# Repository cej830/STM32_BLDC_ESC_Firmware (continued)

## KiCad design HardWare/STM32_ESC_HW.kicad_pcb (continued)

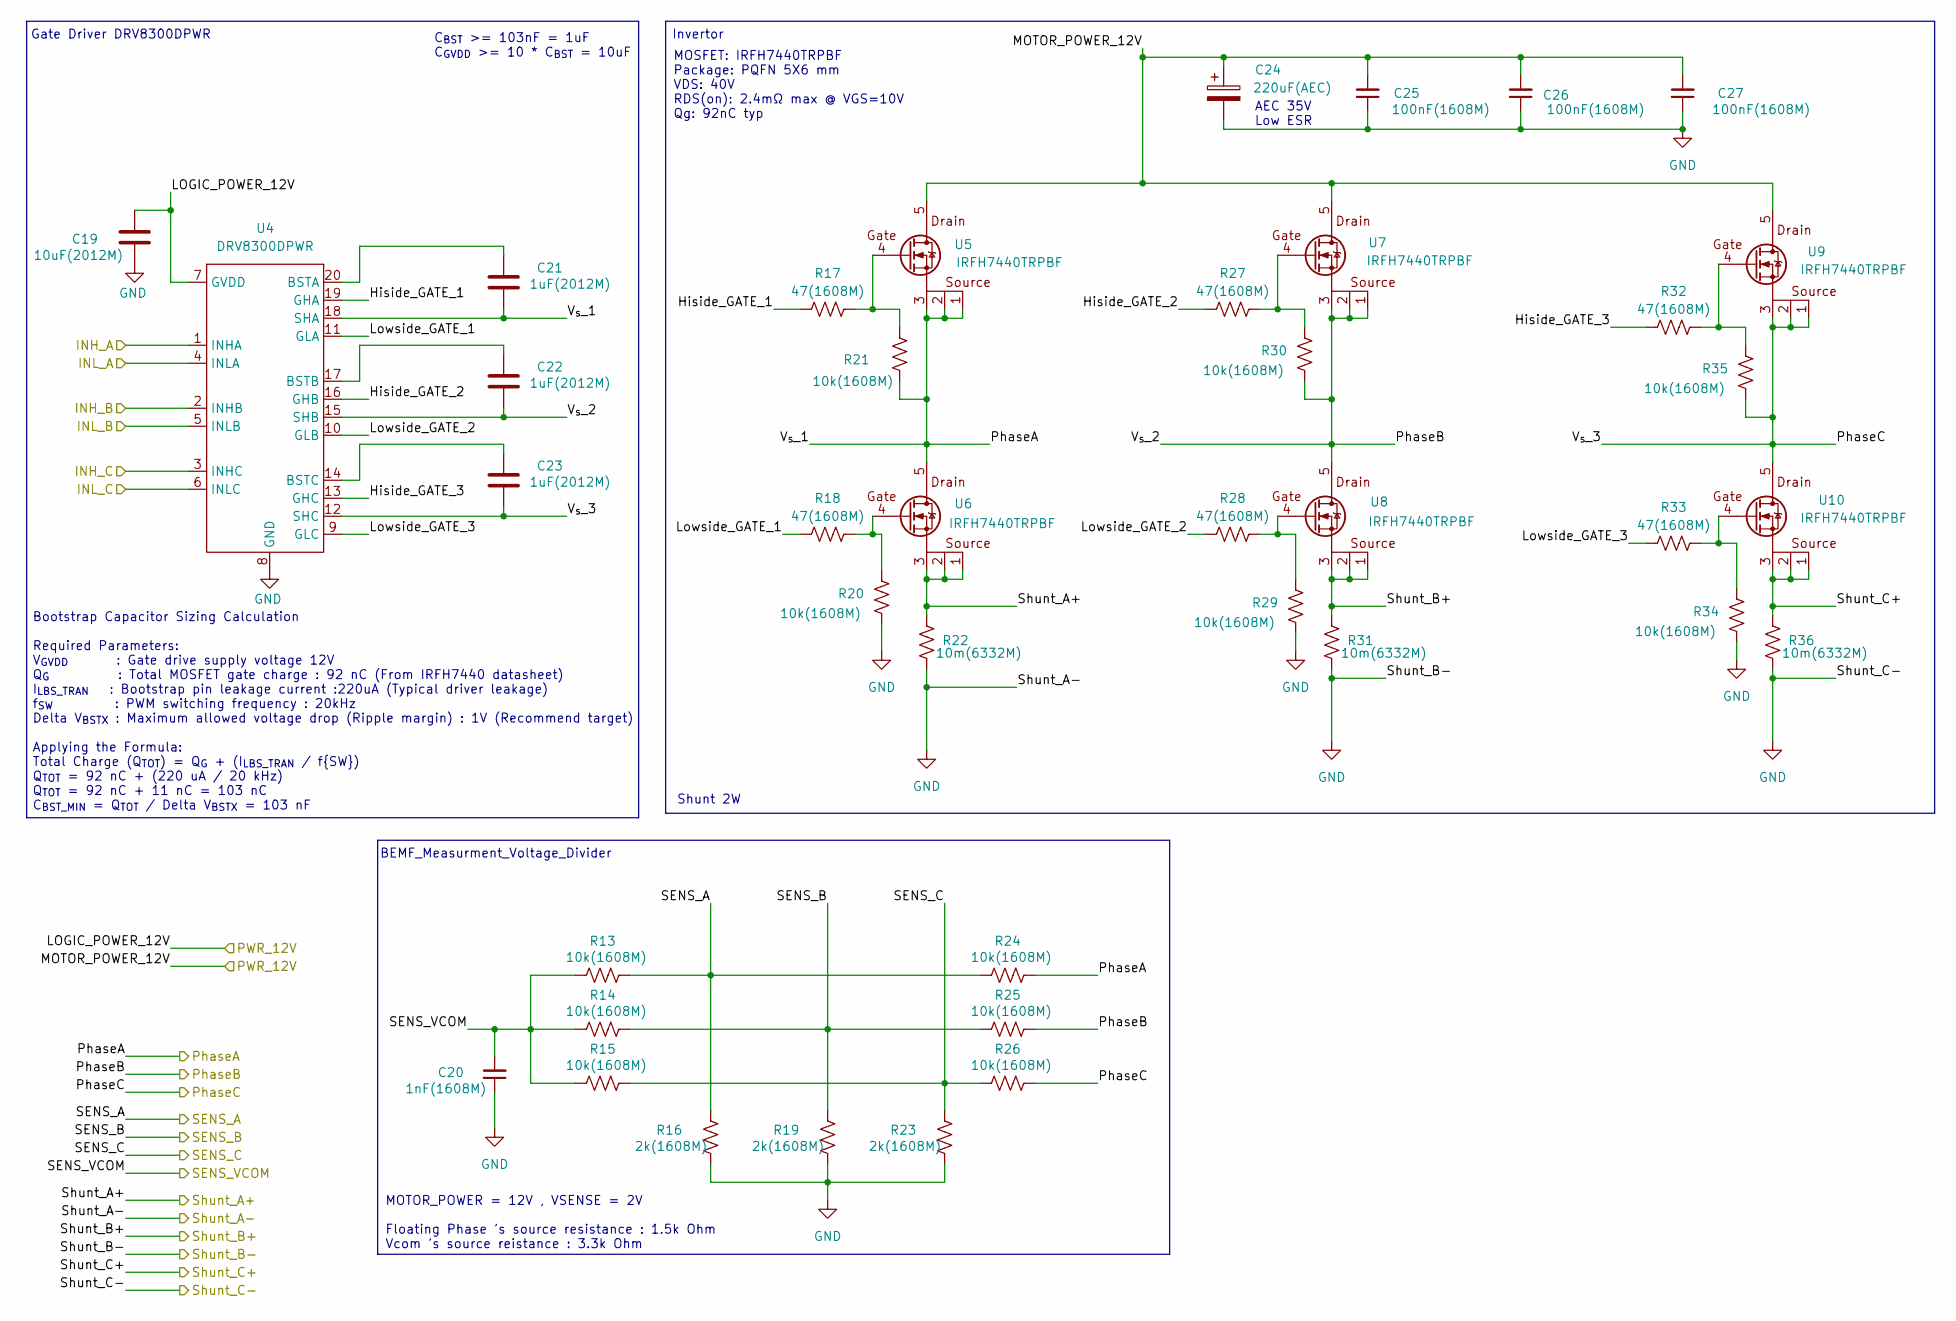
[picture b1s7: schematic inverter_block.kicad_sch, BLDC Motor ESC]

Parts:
C19: 10uF(2012M); C_0805_2012Metric; Part number CL21A106KAYNNNE
C20: 1nF(1608M); C_0603_1608Metric; Part number CL10B102KB8NNNC
C21, C22, C23: 1uF(2012M); C_0805_2012Metric; Part number CL21B105KAFNFNE
C24: 220uF(AEC); CP_Elec_8x10.5; Part number RVT1V221M0810
C25, C26, C27: 100nF(1608M); C_0603_1608Metric; Part number GRM188R71H104KA93D
R13, R14, R15, R20, R21, R24, R25, R26, R29, R30, R34, R35: 10k(1608M); R_0603_1608Metric; Part number 0603WAF1002T5E
R16, R19, R23: 2k(1608M); R_0603_1608Metric; Part number 0603WAF2001T5E
R17, R18, R27, R28, R32, R33: 47(1608M); R_0603_1608Metric; Part number 0603WAF470JT5E
R22, R31, R36: 10m(6332M); Shunt_R_PE2512_7m-910m Ohm_SMD_2512; Part number PE2512FKE7W0R01Z
U4: DRV8300DPWR; DRV8300DPWR 20-TSSOP 6.6mm _ 4.5mm; Part number DRV8300DPWR
U5, U6, U7, U8, U9, U10: IRFH7440TRPBF; PQFN-8-EP_6x5mm_P1.27mm_Generic; Part number IRFH7440TRPBF

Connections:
+12V: C19.1, C24.1, C25.2, C26.2, C27.2, U4.7 (GVDD), U5.5, U7.5, U9.5; also elsewhere on the board
/Inverter_BLOCK/Hiside_GATE_1: R17.1, U4.19 (GHA)
/Inverter_BLOCK/Hiside_GATE_2: R27.1, U4.16 (GHB)
/Inverter_BLOCK/Hiside_GATE_3: R32.1, U4.13 (GHC)
/Inverter_BLOCK/Lowside_GATE_1: R18.1, U4.11 (GLA)
/Inverter_BLOCK/Lowside_GATE_2: R28.1, U4.10 (GLB)
/Inverter_BLOCK/Lowside_GATE_3: R33.1, U4.9 (GLC)
/Inverter_BLOCK/PhaseA: C21.1, R21.2, R24.2, U4.18 (SHA), U5.1, U5.2, U5.3, U6.5; also elsewhere on the board
/Inverter_BLOCK/PhaseB: C22.1, R25.2, R30.2, U4.15 (SHB), U7.1, U7.2, U7.3, U8.5; also elsewhere on the board
/Inverter_BLOCK/PhaseC: C23.1, R26.2, R35.2, U4.12 (SHC), U9.1, U9.2, U9.3, U10.5; also elsewhere on the board
/Inverter_BLOCK/SENS_A: R13.2, R16.2, R24.1; also elsewhere on the board
/Inverter_BLOCK/SENS_B: R14.2, R19.2, R25.1; also elsewhere on the board
/Inverter_BLOCK/SENS_C: R15.2, R23.2, R26.1; also elsewhere on the board
/Inverter_BLOCK/SENS_VCOM: C20.2, R13.1, R14.1, R15.1; also elsewhere on the board
/Inverter_BLOCK/Shunt_A+: R22.1, U6.1, U6.2, U6.3; also elsewhere on the board
/Inverter_BLOCK/Shunt_B+: R31.1, U8.1, U8.2, U8.3; also elsewhere on the board
/Inverter_BLOCK/Shunt_C+: R36.1, U10.1, U10.2, U10.3; also elsewhere on the board
/MCU_BLOCK/PWM_CH1: U4.1 (INHA); also elsewhere on the board
/MCU_BLOCK/PWM_CH1N: U4.4 (INLA); also elsewhere on the board
/MCU_BLOCK/PWM_CH2: U4.2 (INHB); also elsewhere on the board
/MCU_BLOCK/PWM_CH2N: U4.5 (INLB); also elsewhere on the board
/MCU_BLOCK/PWM_CH3: U4.3 (INHC); also elsewhere on the board
/MCU_BLOCK/PWM_CH3N: U4.6 (INLC); also elsewhere on the board
GND: C19.2, C20.1, C24.2, C25.1, C26.1, C27.1, R16.1, R19.1, R20.2, R22.2, R23.1, R29.2, R31.2, R34.2, R36.2, U4.8 (GND); also elsewhere on the board
unnamed: R17.2, R21.1, U5.4
unnamed: R18.2, R20.1, U6.4
unnamed: R27.2, R30.1, U7.4
unnamed: R28.2, R29.1, U8.4
unnamed: R32.2, R35.1, U9.4
unnamed: R33.2, R34.1, U10.4
unnamed: C21.2, U4.20 (BSTA)
unnamed: C22.2, U4.17 (BSTB)
unnamed: C23.2, U4.14 (BSTC)

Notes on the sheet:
BEMF_Measurment_Voltage_Divider
Floating Phase 's source resistance : 1.5k Ohm Vcom 's source reistance : 3.3k Ohm
MOTOR_POWER = 12V , VSENSE = 2V
AEC 35V Low ESR
MOSFET: IRFH7440TRPBF Package: PQFN 5X6 mm VDS: 40V RDS(on): 2.4mΩ max @ VGS=10V Qg: 92nC typ
Shunt 2W
Invertor
C_{BST} >= 103nF = 1uF C_{GVDD} >= 10 * C_{BST} = 10uF
Bootstrap Capacitor Sizing Calculation Required Parameters: V_{GVDD} : Gate drive supply voltage 12V Q_{G} : Total MOSFET gate charge : 92 nC (From IRFH7440 datasheet) I_{LBS_TRAN} : Bootstrap pin leakage current :220uA (Typical driver leakage) f_{SW} : PWM switching frequency : 20kHz Delta V_{BSTX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
Gate Driver DRV8300DPWR

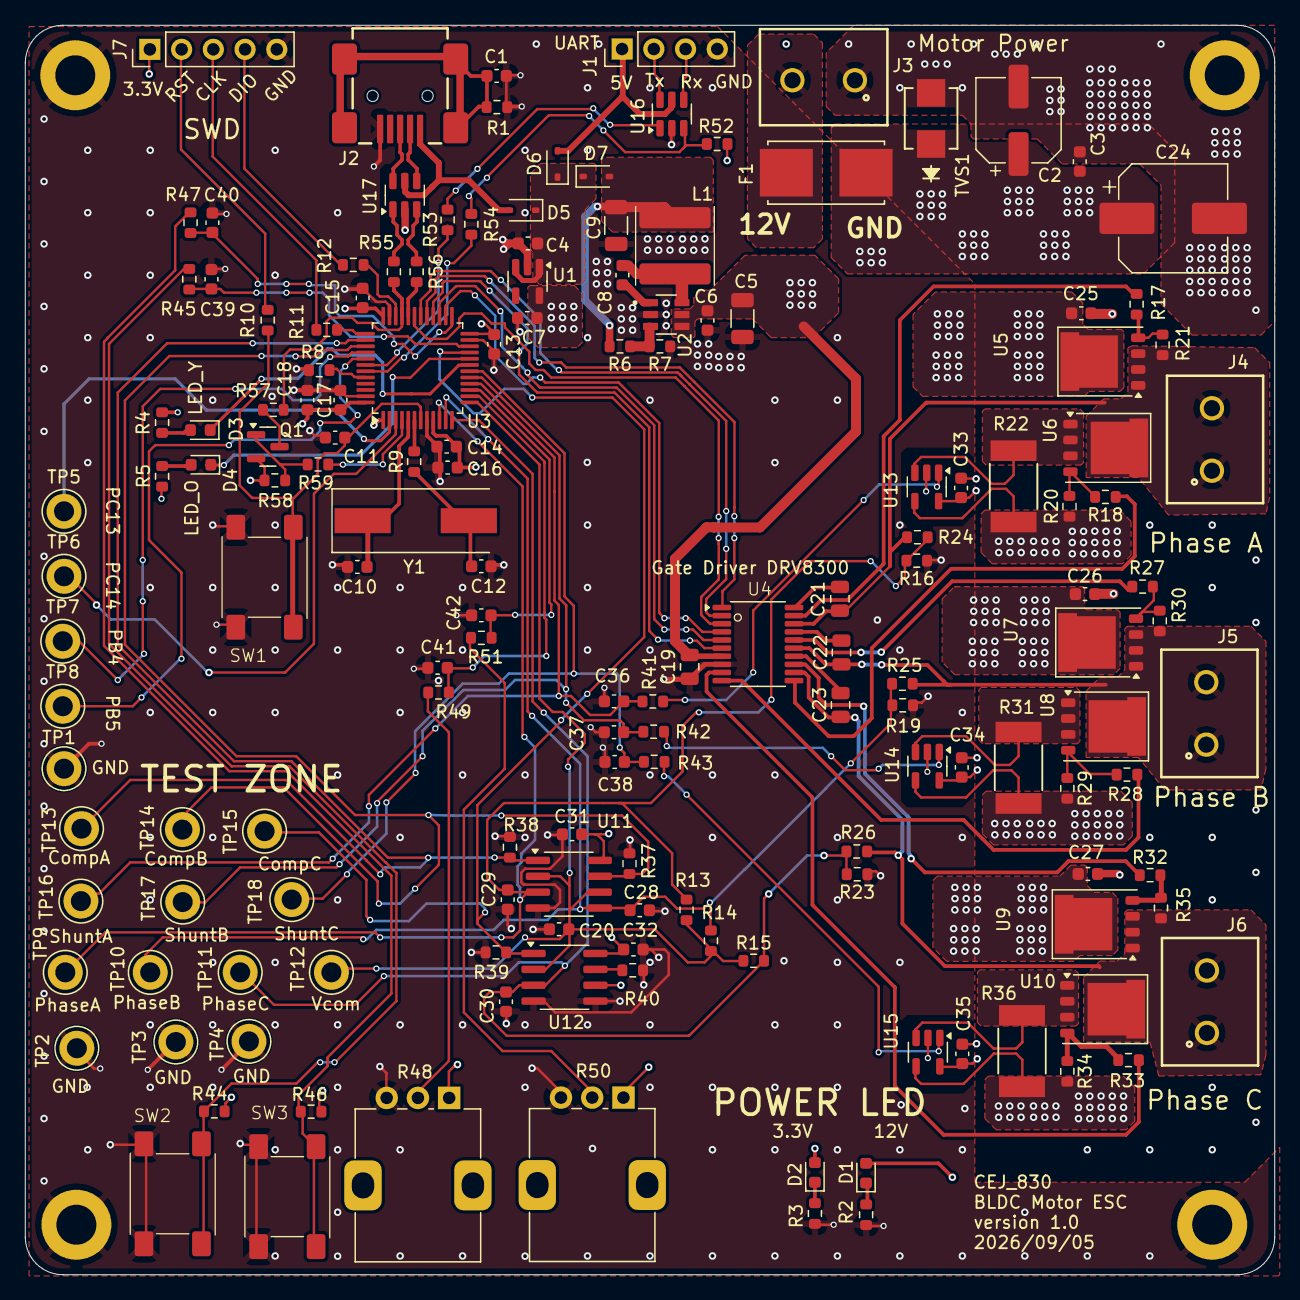
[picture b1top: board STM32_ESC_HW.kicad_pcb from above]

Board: 4 copper layers, 100.0 x 100.0 mm, 162 parts (0 on the bottom side), 96 nets.

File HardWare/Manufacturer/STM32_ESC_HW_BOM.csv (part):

"#","PKG","Reference","Value","설명","Part number","Manufacturer","Qty","Footprint","DNP","Exclude from BOM","Exclude from Board"
"1","SMD_D6.3xL7.7mm","C2","100uF(AEC)","Aluminum Electrolytic, 100uF, 35V, Low ESR","RVT1V101M0607","Honor Elec","1","Capacitor_SMD:CP_Elec_6.3x7.7","","",""
"2","SMD_1206","C5","2.2uF(3216M)","MLCC, 2.2uF, 50V, X7R, ±10%","GRM31CR71H225KA88L","Murata Electronics","1","Capacitor_SMD:C_1206_3216Metric","","",""
"3","SMD_1206","C9","22uF(3216M)","MLCC, 22uF, 10V, X7R, ±10%","GRM31CR71A226KE15L","Murata Electronics","1","Capacitor_SMD:C_1206_3216Metric","","",""
"4","SMD_0603","C14","10nF(1608M)","MLCC, 10nF, 50V, X7R, ±10%","CL10B103KB8NNNC","Samsung Electro-Mechanics","1","Capacitor_SMD:C_0603_1608Metric","","",""
"5","SMD_0805","C19","10uF(2012M)","MLCC, 10uF, 25V, X5R, ±10%","CL21A106KAYNNNE","Samsung Electro-Mechanics","1","Capacitor_SMD:C_0805_2012Metric","","",""
"6","SMD_D8_L10.2mm","C24","220uF(AEC)","Aluminum Electrolytic, 220uF, 35V, Low ESR","RVT1V221M0810","Honor Elec","1","Capacitor_SMD:CP_Elec_8x10.5","","",""
"7","SMD_0603","C1,C3,C6,C8,C11,C13,C15,C17,C25,C26,C27,C31,C32,C33,C34,C35,C39,C40,C41,C42","100nF(1608M)","MLCC, 100nF, 50V, X7R, ±10%","GRM188R71H104KA93D","Murata Electronics","20","Capacitor_SMD:C_0603_1608Metric","","",""
"8","SMD_0603","C10,C12","20pF(1608M)","MLCC, 20pF, 50V, C0G, ±5%","CL10C200JB8NNNC","Samsung Electro-Mechanics","2","Capacitor_SMD:C_0603_1608Metric","","",""
"9","SMD_0603","C20,C36,C37,C38","1nF(1608M)","MLCC, 1nF, 50V, X7R, ±10%","CL10B102KB8NNNC","Samsung Electro-Mechanics","4","Capacitor_SMD:C_0603_1608Metric","","",""
"10","SMD_0805","C21,C22,C23","1uF(2012M)","MLCC, 1uF, 25V, X5R, ±10%","CL21B105KAFNFNE","Samsung Electro-Mechanics","3","Capacitor_SMD:C_0805_2012Metric","","",""
"11","SMD_0603","C28,C29,C30","2.2nF(1608M)","MLCC, 2.2nF, 50V, X7R, ±10%","CL10B222KB8NNNC","Samsung Electro-Mechanics","3","Capacitor_SMD:C_0603_1608Metric","","",""
"12","SMD_0603","C4,C7,C16,C18","1uF(1608M)","MLCC, 1uF, 25V, X5R, ±10%","CL10A105KA8NNNC","Samsung Electro-Mechanics","4","Capacitor_SMD:C_0603_1608Metric","","",""
"13","SMD_0603","D1","GREEN@5mA","LED, Green, Vf 2.6-3.6V, 20mA, 900mcd","NCD0603G1","Foshan NationStar Optoelectronics","1","LED_SMD:LED_0603_1608Metric","","",""
"14","SMD_0603","D2","RED@5mA","LED, Red, Vf 1.6-2.6V, 25mA, 220mcd","NCD0603R1","Foshan NationStar Optoelectronics","1","LED_SMD:LED_0603_1608Metric","","",""
"15","SMD_0603","D3","YELLOW@5mA","LED, Yellow, Vf 1.6-2.6V, 25mA, 60mcd","NCD0603C1","Foshan NationStar Optoelectronics","1","LED_SMD:LED_0603_1608Metric","","",""
"16","SMD_0603","D4","ORANGE@5mA","LED, Orange, Vf 1.5-2.6V, 25mA, 250mcd","NCD0603O1","Foshan NationStar Optoelectronics","1","LED_SMD:LED_0603_1608Metric","","",""
"17","SMD_SOD-323","D5,D6,D7","1SS404","Scohotty Diode, Vf 0.45V, 300mA, 20V","1SS404","Jiangsu Changjing Electronics Technology Co., Ltd.","3","Diode_SMD:D_SOD-323","","",""
"18","SMD_9.7x5mm","F1","0154002.DRT","SMD Fuse with Holder, 2A, 125V, Slow-Blow","0154002.DRT","Littelfuse","1","my_lib:FUSE_154 Series OMNI-BLOK® Fuse and Holder Assembly","","",""
"19","","H1,H2,H3,H4","MountingHole_Pad","Mounting Hole with connection","","","4","MountingHole:MountingHole_3.2mm_M3_DIN965_Pad","","BOM에서 제외됨",""
"20","TH_Pitch2.54mm_1x4P","J1","UART","Pin Header, 1x4P, 2.54mm, Male, Vertical","254PZ-1x4P-V","LXWCONN","1","Connector_PinHeader_2.54mm:PinHeader_1x04_P2.54mm_Vertical","","",""
"21","SMD_Mini-B","J2","USB_B_Mini","USB 2.0 Mini-B Receptacle, Female, SMD, Right Angle","920-462A2021S10101","Jing Extension of the Electronic Co.","1","my_lib:USB_Mini B 920-462A2021S10101","","",""
"22","TH_Pitch5.00mm_2P","J3","PWR","Terminal Block, 2-Pos, Horizontal, 16A, 12-30AWG","691137710002","  Würth Elektronik","1","my_lib:TERM BLK 2POS SIDE ENTRY 5MM PCB","","",""
"23","TH_Pitch5.00mm_2P","J4","Phase A","Terminal Block, 2-Pos, Horizontal, 16A, 12-30AWG","691137710002","  Würth Elektronik","1","my_lib:TERM BLK 2POS SIDE ENTRY 5MM PCB","","",""
"24","TH_Pitch5.00mm_2P","J5","Phase B","Terminal Block, 2-Pos, Horizontal, 16A, 12-30AWG","691137710002","  Würth Elektronik","1","my_lib:TERM BLK 2POS SIDE ENTRY 5MM PCB","","",""
"25","TH_Pitch5.00mm_2P","J6","Phase C","Terminal Block, 2-Pos, Horizontal, 16A, 12-30AWG","691137710002","  Würth Elektronik","1","my_lib:TERM BLK 2POS SIDE ENTRY 5MM PCB","","",""
"26","TH_Pitch2.54mm_1x5P","J7","Conn_01x05","Pin Header, 1x5P, 2.54mm, Male, Vertical","2.54-1*5","ZHOURI","1","Connector_PinHeader_2.54mm:PinHeader_1x05_P2.54mm_Vertical","","",""
"27","SMD_6x6mm","L1","18uH @SMNR6028-180MT","Shielded Power Inductor, 18uH, ±20%, Isat 1.52A, Irms 1.45A, DCR 169mΩ","SMNR6028-180MT","SXN(Shun Xiang Nuo Elec)","1","my_lib:Inductor SMNR6028-180MT","","",""
"28","SMD_SOT-23","Q1","UMW AO3401A (PMOS)","P-MOSFET transistor, gate/source/drain","AO3401A","UMW(Youtai Semiconductor Co., Ltd.)","1","Package_TO_SOT_SMD:SOT-23","","",""
"29","SMD_0603","R2","1.8k(1608M)","Thick Film Resistor, 1.8kΩ, 1/10W, ±1%","0603WAJ0182T5E","UNI-ROYAL(Uniroyal Elec)","1","Resistor_SMD:R_0603_1608Metric","","",""
"30","SMD_0603","R6","88.7k(1608M)","Thick Film Resistor, 88.7kΩ, 1/10W, ±1%","0603WAF8872T5E","UNI-ROYAL(Uniroyal Elec)","1","Resistor_SMD:R_0603_1608Metric","","",""
"31","SMD_0603","R7","22.1k(1608M)","Thick Film Resistor, 22.1kΩ, 1/10W, ±1%","0603WAF2212T5E","UNI-ROYAL(Uniroyal Elec)","1","Resistor_SMD:R_0603_1608Metric","","",""
"32","SMD_0603","R9","0(1608M)","Thick Film Resistor, 0Ω, 1/10W, ±1%","0603WAF0000T5E","UNI-ROYAL(Uniroyal Elec)","1","Resistor_SMD:R_0603_1608Metric","","",""
"33","SMD_0603","R57","1.5k(1608M)","Thick Film Resistor, 1.5kΩ, 1/10W, ±1%","0603WAF1501T5E","UNI-ROYAL(Uniroyal Elec)","1","Resistor_SMD:R_0603_1608Metric","","",""
"34","SMD_0603","R1,R59","330(1608M)","Thick Film Resistor, 330Ω, 1/10W, ±1%","0603WAF3300T5E","UNI-ROYAL(Uniroyal Elec)","2","Resistor_SMD:R_0603_1608Metric","","",""
"35","SMD_0603","R10,R11,R12","33(1608M)","Thick Film Resistor, 33Ω, 1/10W, ±1%","0603WAF330JT5E","UNI-ROYAL(Uniroyal Elec)","3","Resistor_SMD:R_0603_1608Metric","","",""
"36","SMD_0603","R16,R19,R23","2k(1608M)","Thick Film Resistor, 2kΩ, 1/10W, ±1%","0603WAF2001T5E","UNI-ROYAL(Uniroyal Elec)","3","Resistor_SMD:R_0603_1608Metric","","",""
"37","SMD_0603","R17,R18,R27,R28,R32,R33","47(1608M)","Thick Film Resistor, 47Ω, 1/10W, ±1%","0603WAF470JT5E","UNI-ROYAL(Uniroyal Elec)","6","Resistor_SMD:R_0603_1608Metric","","",""
"38","SMD_2512","R22,R31,R36","10m(6332M)","Current Sense Metal Film Resistor, 10mΩ, 2W, ±1%, ±50ppm/℃","PE2512FKE7W0R01Z","YAGEO","3","my_lib:Shunt_R_PE2512_7m-910m Ohm_SMD_2512","","",""
"39","SMD_0603","R3,R4,R5","270(1608M)","Thick Film Resistor, 270Ω, 1/10W, ±5%","0603WAJ0271T5E","UNI-ROYAL(Uniroyal Elec)","3","Resistor_SMD:R_0603_1608Metric","","",""
"40","SMD_0603","R41,R42,R43","1k(1608M)","Thick Film Resistor, 1kΩ, 1/10W, ±1%","0603WAF1001T5E","UNI-ROYAL(Uniroyal Elec)","3","Resistor_SMD:R_0603_1608Metric","","",""
"41","TH_ALPS_RK09K","R48,R50","10k(pot THT)","Rotary Potentiometer, 10kΩ, ±20%, Linear , Top Adjust, TH","RK09K1130AAU","ALPSALPINE","2","my_lib:Potentiometer_Alps_RK09K_Single_Vertical","","",""
"42","SMD_0603","R53,R54,R55,R56","22(1608M)","Thick Film Resistor, 22Ω, 1/10W, ±1%","0603WAF220JT5E","UNI-ROYAL(Uniroyal Elec)","4","Resistor_SMD:R_0603_1608Metric","","",""
"43","SMD_0603","R8,R13,R14,R15,R20,R21,R24,R25,R26,R29,R30,R34,R35,R37,R38,R39,R40,R44,R45,R46,R47,R49,R51,R52,R58","10k(1608M)","Thick Film Resistor, 10kΩ, 1/10W, ±1%","0603WAF1002T5E","UNI-ROYAL(Uniroyal Elec)","25","Resistor_SMD:R_0603_1608Metric","","",""
"44","SMD_4P_6x6mm","SW1,SW2,SW3","SW_SPST","Tactile Switch, SPST, 12V 50mA, 1.6N, H=5mm","UK-B0228-G5-160-JZ","USAKRO","3","my_lib:Button_Switch_SMD SW_Push_1P1T SMD-4P,6x6mm","","",""
"45","TH_3.2mm","TP12","5121 G","Test Ring, Green","RH-5121","ronghe","1","TestPoint:TestPoint_Keystone_5005-5009_Compact","","",""
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
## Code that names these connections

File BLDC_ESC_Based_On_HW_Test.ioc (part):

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Mcu.Name=STM32F103C(8-B)Tx
Mcu.Package=LQFP48
Mcu.UserName=STM32F103C8Tx
PA0-WKUP.GPIOParameters=GPIO_Label
PA0-WKUP.GPIO_Label=ADC_PhaseA
PA0-WKUP.Signal=ADCx_IN0
PA1.GPIOParameters=GPIO_Label
PA1.GPIO_Label=ADC_PhaseB
PA1.Signal=ADCx_IN1
PA10.GPIOParameters=GPIO_Label
PA10.GPIO_Label=PWM_CH3
PA10.Signal=S_TIM1_CH3
PA11.Mode=Device
PA11.Signal=USB_DM
PA12.Mode=Device
PA12.Signal=USB_DP
PA13.Mode=Serial_Wire
PA13.Signal=SYS_JTMS-SWDIO
PA14.Mode=Serial_Wire
PA14.Signal=SYS_JTCK-SWCLK
PA15.GPIOParameters=GPIO_Label
PA15.GPIO_Label=TIM2_IC_COMPA
PA15.Signal=S_TIM2_CH1_ETR
PA2.GPIOParameters=GPIO_Label
PA2.GPIO_Label=ADC_PhaseC
PA2.Signal=ADCx_IN2
PA3.GPIOParameters=GPIO_Label
PA3.GPIO_Label=ADC_Vcom
PA3.Signal=ADCx_IN3
PA4.GPIOParameters=GPIO_Label
PA4.GPIO_Label=ADC_Poten1
PA4.Signal=ADCx_IN4
PA5.GPIOParameters=GPIO_Label
PA5.GPIO_Label=ADC_Poten2
PA5.Signal=ADCx_IN5
PA6.GPIOParameters=GPIO_Label
PA6.GPIO_Label=ADC_ShuntA
PA6.Signal=ADCx_IN6
PA7.GPIOParameters=GPIO_Label
PA7.GPIO_Label=ADC_ShuntB
PA7.Signal=ADCx_IN7
PA8.GPIOParameters=GPIO_Label
PA8.GPIO_Label=PWM_CH1
PA8.Signal=S_TIM1_CH1
PA9.GPIOParameters=GPIO_Label
PA9.GPIO_Label=PWM_CH2
PA9.Signal=S_TIM1_CH2
PB0.GPIOParameters=GPIO_Label
PB0.GPIO_Label=ADC_ShuntC
PB0.Signal=ADCx_IN8
PB1.GPIOParameters=GPIO_Label
PB1.GPIO_Label=LED_YELLOW
PB1.Signal=GPIO_Output
PB10.GPIOParameters=GPIO_Label
PB10.GPIO_Label=TIM2_IC_COMPC
PB10.Signal=S_TIM2_CH3
PB11.GPIOParameters=GPIO_Label,GPIO_ModeDefaultEXTI
PB11.GPIO_Label=USER_BTN_1
PB11.GPIO_ModeDefaultEXTI=GPIO_MODE_IT_FALLING
PB11.Signal=GPXTI11
PB12.GPIOParameters=GPIO_Label
PB12.GPIO_Label=USER_BTN_2
PB12.Signal=GPIO_Input
PB13.GPIOParameters=GPIO_Label
PB13.GPIO_Label=PWM_CH1N
PB13.Mode=PWM Generation1 CH1 CH1N
PB13.Signal=TIM1_CH1N
PB14.GPIOParameters=GPIO_Label
PB14.GPIO_Label=PWM_CH2N
PB14.Mode=PWM Generation2 CH2 CH2N
PB14.Signal=TIM1_CH2N
PB15.GPIOParameters=GPIO_Label
PB15.GPIO_Label=PWM_CH3N
PB15.Mode=PWM Generation3 CH3 CH3N
PB15.Signal=TIM1_CH3N
PB2.GPIOParameters=GPIO_Label
PB2.GPIO_Label=LED_ORANGE
PB2.Signal=GPIO_Output
PB3.GPIOParameters=GPIO_Label
PB3.GPIO_Label=TIM2_IC_COMPB
PB3.Signal=S_TIM2_CH2
PB4.GPIOParameters=GPIO_Label
PB4.GPIO_Label=DEBUG_PB4
PB4.Signal=GPIO_Output
PB5.GPIOParameters=GPIO_Label
PB5.GPIO_Label=DEBUG_PB5
PB5.Signal=GPIO_Output
PB6.Mode=Asynchronous
PB6.Signal=USART1_TX
PB7.Mode=Asynchronous
PB7.Signal=USART1_RX
PC13-TAMPER-RTC.GPIOParameters=GPIO_Label
PC13-TAMPER-RTC.GPIO_Label=DEBUG_PC13
PC13-TAMPER-RTC.Signal=GPIO_Output
PC14-OSC32_IN.GPIOParameters=GPIO_Label
PC14-OSC32_IN.GPIO_Label=DEBUG_PC14
PC14-OSC32_IN.Signal=GPIO_Output
PC15-OSC32_OUT.GPIOParameters=GPIO_Label
PC15-OSC32_OUT.GPIO_Label=USB_DP_PullUp
PC15-OSC32_OUT.Signal=GPIO_Output
PD0-OSC_IN.Mode=HSE-External-Oscillator
PD0-OSC_IN.Signal=RCC_OSC_IN
PD1-OSC_OUT.Mode=HSE-External-Oscillator
PD1-OSC_OUT.Signal=RCC_OSC_OUT
RCC.SYSCLKFreq_VALUE=72000000
RCC.SYSCLKSource=RCC_SYSCLKSOURCE_PLLCLK
board=custom

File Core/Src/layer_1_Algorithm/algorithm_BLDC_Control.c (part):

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// 현재 스텝에 해당하는 BEMF 값을 계산 하는 함수
static inline int16_t Calculate_BEMF(uint8_t step)
{
	uint16_t PhaseA, PhaseB, PhaseC, Vcom = 0;
	Driver_BLDC_HW_GetPhaseV(&PhaseA, &PhaseB, &PhaseC);
	Vcom = (uint16_t)(((uint32_t)PhaseA + (uint32_t)PhaseB + (uint32_t)PhaseC)/3);
	
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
